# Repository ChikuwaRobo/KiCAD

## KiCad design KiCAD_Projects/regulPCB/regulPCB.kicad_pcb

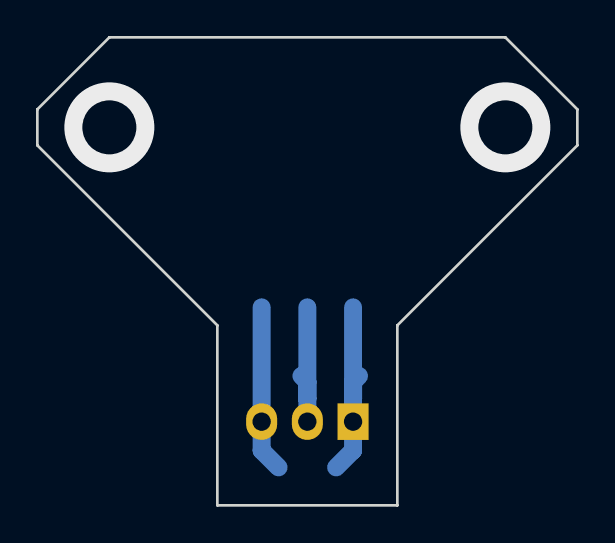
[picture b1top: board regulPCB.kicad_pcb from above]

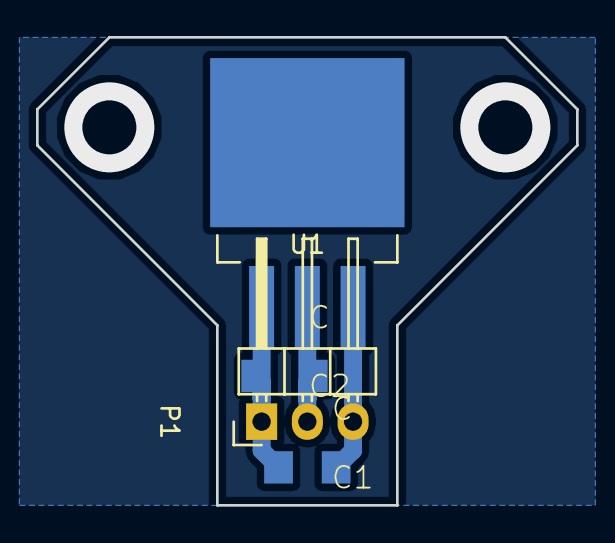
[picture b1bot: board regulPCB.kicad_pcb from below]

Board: 2 copper layers, 30.0 x 26.0 mm, 4 parts (4 on the bottom side), 3 nets.

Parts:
C1, C2: C; C3216
P1: CONN_01X03; Pin_Header_Angled_1x03
U1: LM1084IT-5.0/NOPB; TO-263-3Lead

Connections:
unnamed: C1.1, P1.3, U1.3
unnamed: C1.2, C2.2, P1.1, U1.1
unnamed: C2.1, P1.2, U1.2

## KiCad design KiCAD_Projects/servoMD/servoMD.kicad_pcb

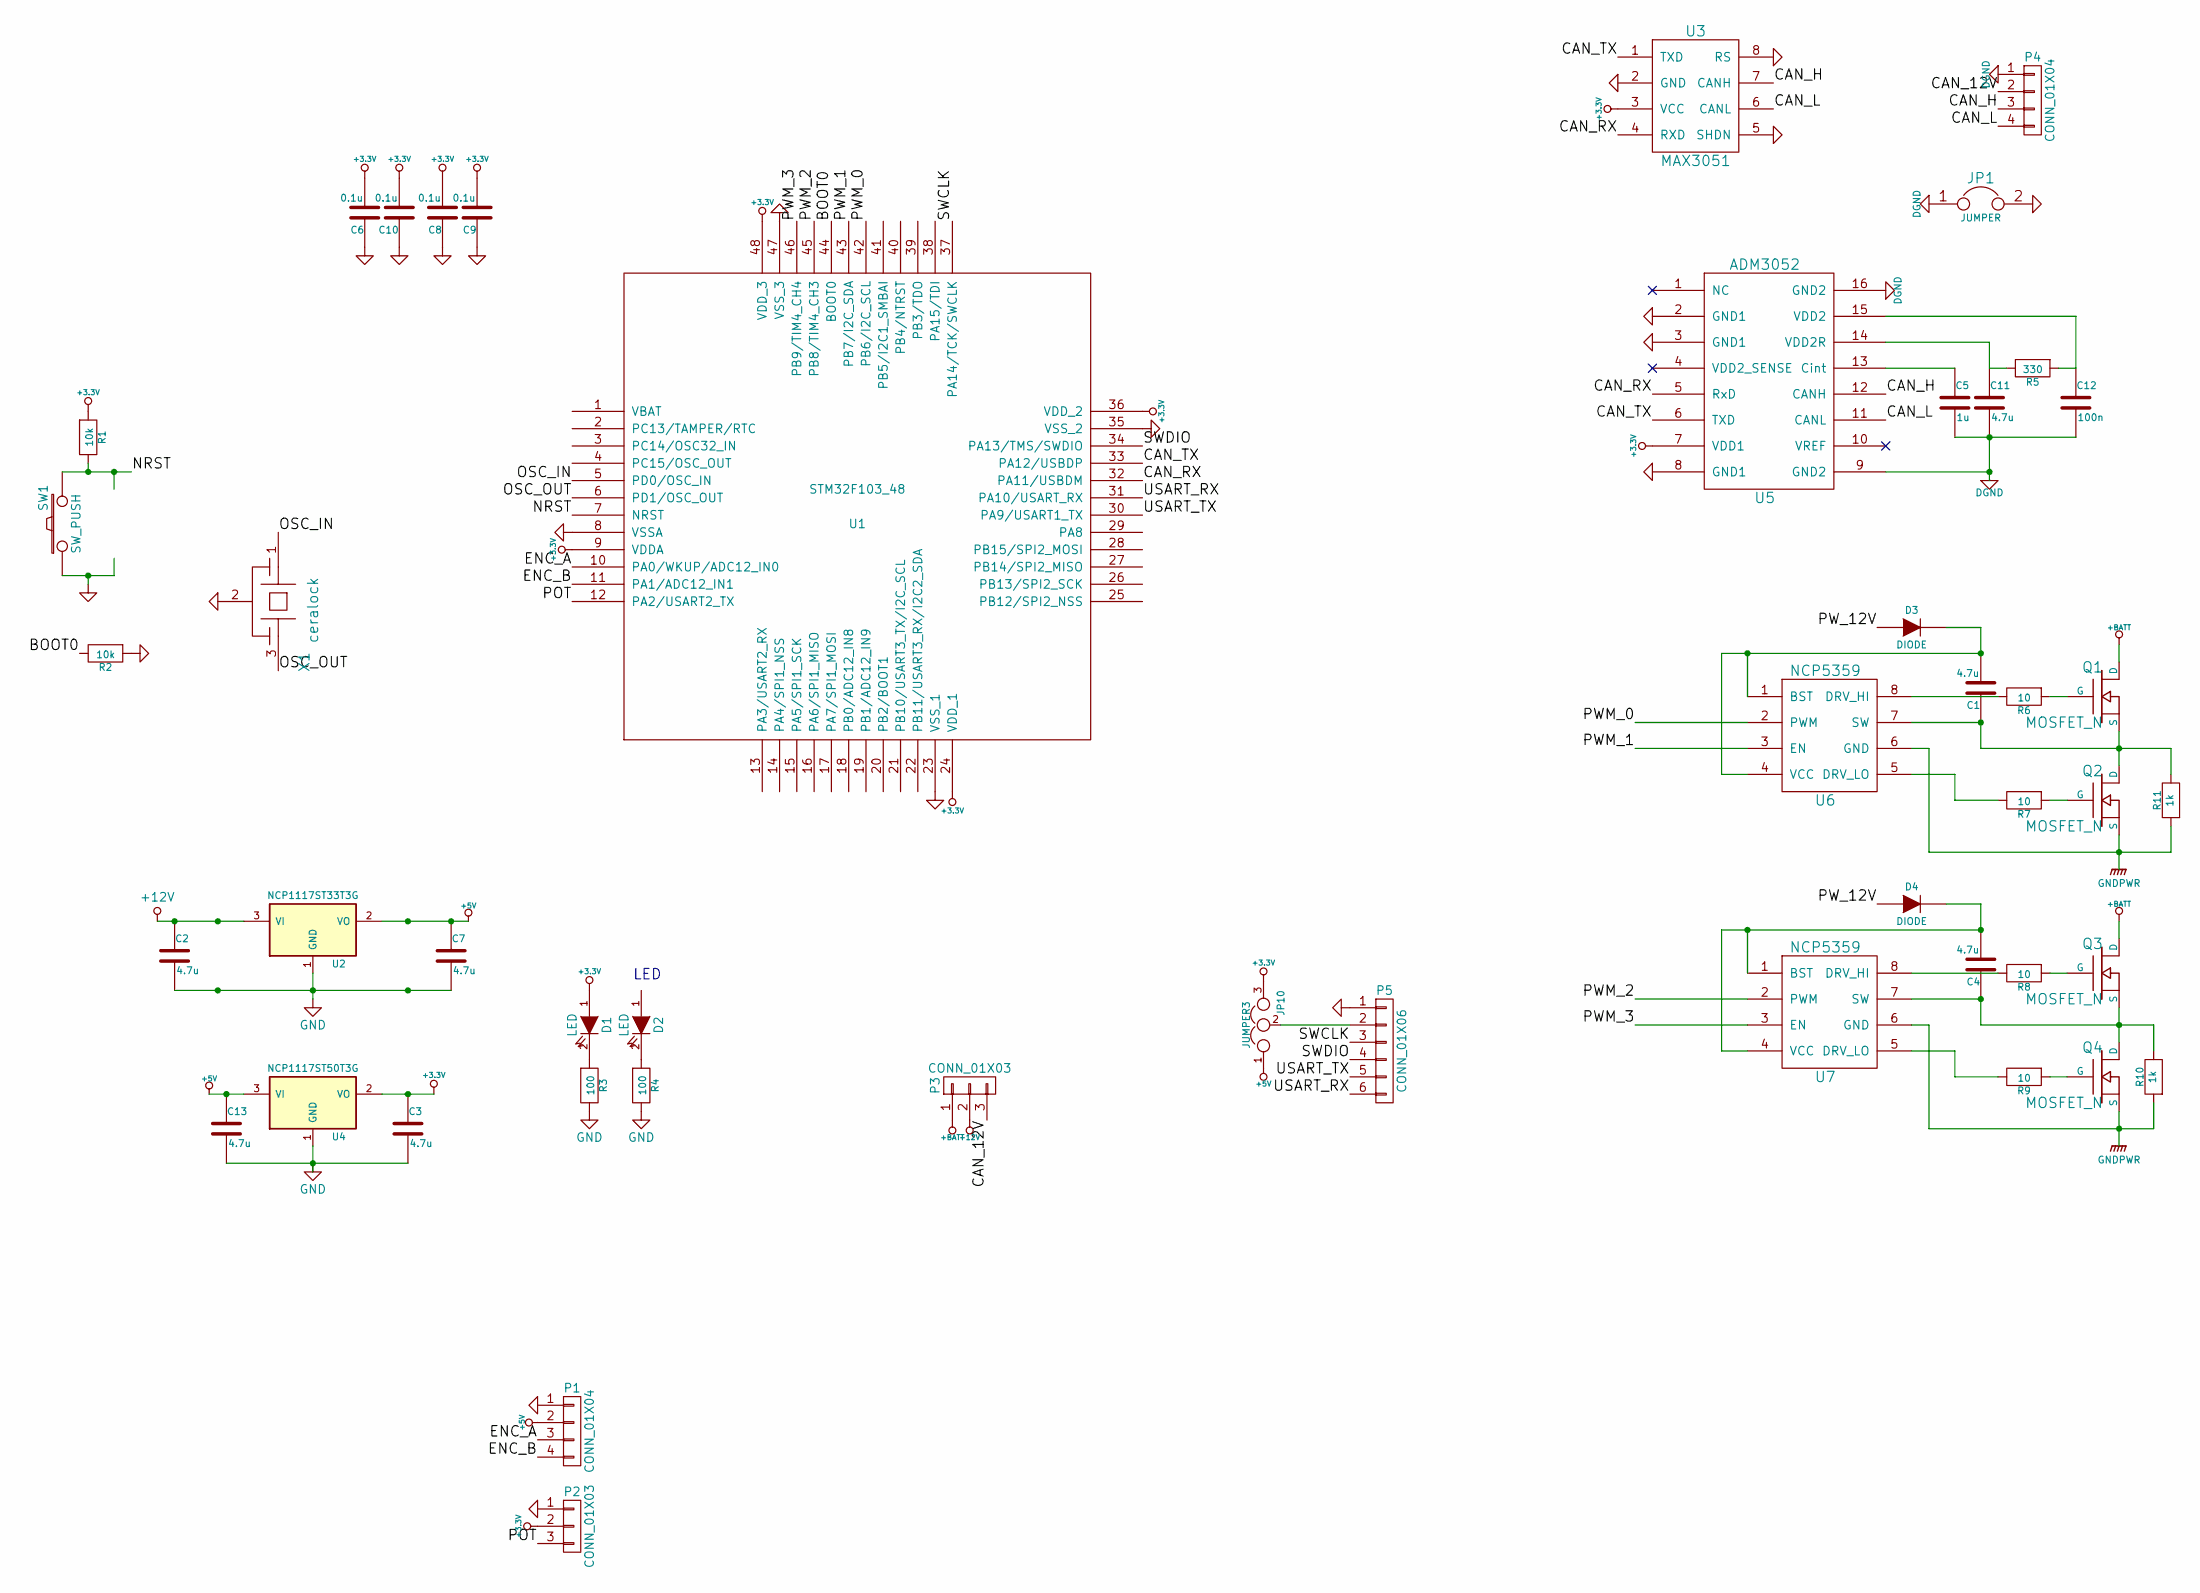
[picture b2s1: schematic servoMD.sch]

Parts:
C1, C2, C3, C4, C7, C11, C13: 4.7u; C3216_S
C5: 1u; C1608_WP_S
C6, C8, C9, C10: 0.1u; C1608_WP_S
C12: 100n; C1608_WP_S
D1, D2: LED; LED_0805
D3, D4: DIODE; C1608_WP_S
JP1: JUMPER; GS2
JP10: JUMPER3; GS3
P1, P4: CONN_01X04; XA_4T
P2: CONN_01X03; XA_3T
P3: CONN_01X03; Pin_Header_Straight_1x03
P5: CONN_01X06; ZH_6T
Q1, Q2, Q3, Q4: MOSFET_N; SOT-428_GDS
R1, R2: 10k; C1608_WP_S
R3, R4: 100; C1608_WP_S
R5: 330; C3225
R6, R7, R8, R9: 10; C1608_WP_S
R10, R11: 1k; C1608_WP_S
SW1: SW_PUSH; SW_SPST_EVQPE1
U1: STM32F103_48; LQFP-48_7x7mm_Pitch0.5mm
U2: NCP1117ST33T3G; SOT-223_reg
U3: MAX3051; SOIC-8_3.9x4.9mm_Pitch1.27mm_S
U4: NCP1117ST50T3G; SOT-223_reg
U5: ADM3052; SOIC-16_7.5x10.3mm_Pitch1.27mm
U6, U7: NCP5359; SOIC-8_3.9x4.9mm_Pitch1.27mm
X1: ceralock; Resonator_3×1.3mm

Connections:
+3.3V: C3.1, C6.2, C8.2, C9.2, C10.2, D1.1 (A), JP10.3, P2.2, R1.1, U1.9 (VDDA), U1.24 (VDD_1), U1.36 (VDD_2), U1.48 (VDD_3), U3.3 (VCC), U4.2 (VO), U5.7 (VDD1)
+5V: C7.1, C13.1, JP10.1, P1.2, U2.2 (VO), U4.3 (VI)
+12V: C2.1, P3.2, U2.3 (VI)
+BATT: P3.1, Q1.D, Q3.D
/BOOT0: R2.2, U1.44 (BOOT0)
/CAN_12V: P3.3, P4.2
/CAN_H: P4.3, U3.7 (CANH), U5.12 (CANH)
/CAN_L: P4.4, U3.6 (CANL), U5.11 (CANL)
/CAN_RX: U1.32 (PA11/USBDM), U3.4 (RXD), U5.5 (RxD)
/CAN_TX: U1.33 (PA12/USBDP), U3.1 (TXD), U5.6 (TXD)
/ENC_A: P1.3, U1.10 (PA0/WKUP/ADC12_IN0)
/ENC_B: P1.4, U1.11 (PA1/ADC12_IN1)
/NRST: R1.2, SW1.2, U1.7 (NRST)
/OSC_IN: U1.5 (PD0/OSC_IN), X1.1
/OSC_OUT: U1.6 (PD1/OSC_OUT), X1.3
/POT: P2.3, U1.12 (PA2/USART2_TX)
/PWM_0: U1.42 (PB6/I2C_SCL), U6.2 (PWM)
/PWM_1: U1.43 (PB7/I2C_SDA), U6.3 (EN)
/PWM_2: U1.45 (PB8/TIM4_CH3), U7.2 (PWM)
/PWM_3: U1.46 (PB9/TIM4_CH4), U7.3 (EN)
/PW_12V: D3.2 (A), D4.2 (A)
/SWCLK: P5.3, U1.37 (PA14/TCK/SWCLK)
/SWDIO: P5.4, U1.34 (PA13/TMS/SWDIO)
/USART_RX: P5.6, U1.31 (PA10/USART_RX)
/USART_TX: P5.5, U1.30 (PA9/USART1_TX)
DGND: C5.2, C11.2, C12.2, JP1.1, P4.1, U5.9 (GND2), U5.16 (GND2)
GND: C2.2, C3.2, C6.1, C7.2, C8.1, C9.1, C10.1, C13.2, JP1.2, P1.1, P2.1, P5.1, R2.1, R3.2, R4.2, SW1.1, U1.8 (VSSA), U1.23 (VSS_1), U1.35 (VSS_2), U1.47 (VSS_3), U2.1 (GND), U3.2 (GND), U3.5 (SHDN), U3.8 (RS), U4.1 (GND), U5.2 (GND1), U5.3 (GND1), U5.8 (GND1), X1.2
GNDPWR: Q2.S, Q4.S, R10.1, R11.1, U6.6 (GND), U7.6 (GND)
unnamed: C1.1, Q1.S, Q2.D, R11.2, U6.7 (SW)
unnamed: C1.2, D3.1 (K), U6.1 (BST), U6.4 (VCC)
unnamed: C4.1, Q3.S, Q4.D, R10.2, U7.7 (SW)
unnamed: C4.2, D4.1 (K), U7.1 (BST), U7.4 (VCC)
unnamed: C5.1, U5.13 (Cint)
unnamed: C11.1, R5.2, U5.14 (VDD2R)
unnamed: C12.1, R5.1, U5.15 (VDD2)
unnamed: D1.2 (K), R3.1
unnamed: D2.2 (K), R4.1
unnamed: JP10.2, P5.2
unnamed: Q1.G, R6.1
unnamed: Q2.G, R7.1
unnamed: Q3.G, R8.1
unnamed: Q4.G, R9.1
unnamed: R6.2, U6.8 (DRV_HI)
unnamed: R7.2, U6.5 (DRV_LO)
unnamed: R8.2, U7.8 (DRV_HI)
unnamed: R9.2, U7.5 (DRV_LO)

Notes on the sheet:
LED

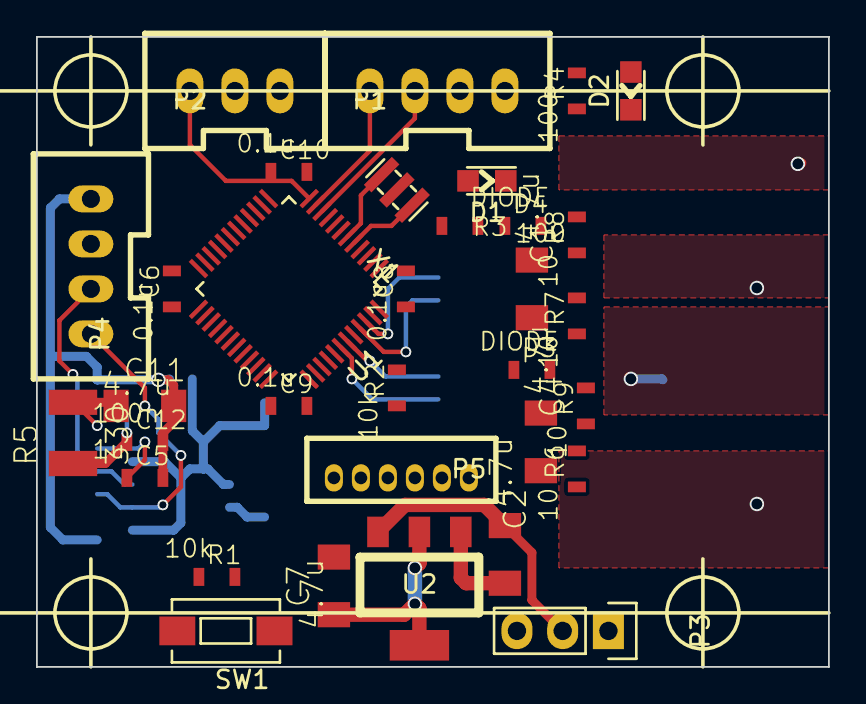
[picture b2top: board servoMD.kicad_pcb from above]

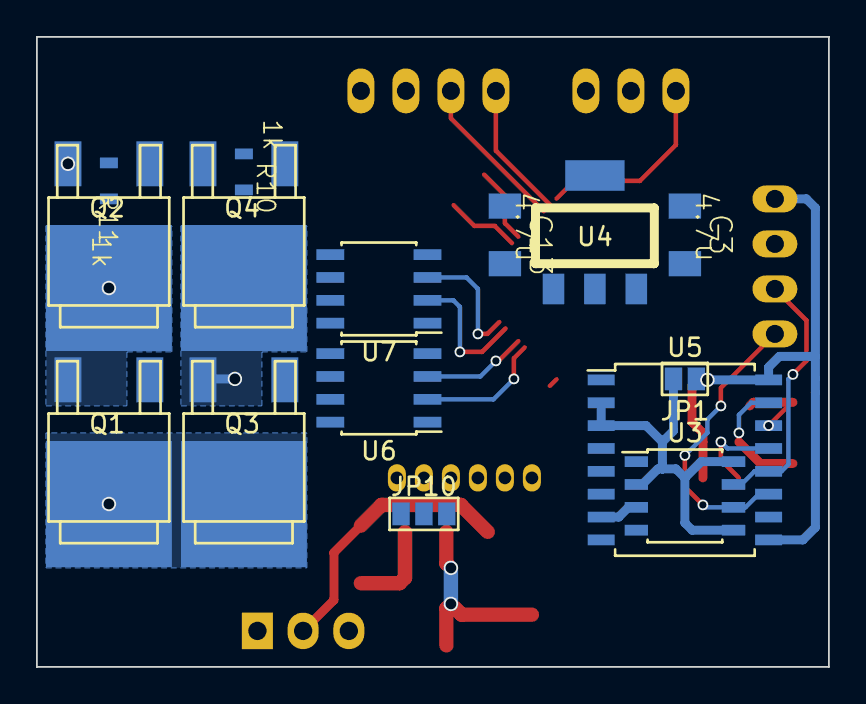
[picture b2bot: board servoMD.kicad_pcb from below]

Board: 2 copper layers, 44.0 x 35.0 mm, 48 parts (15 on the bottom side), 46 nets.

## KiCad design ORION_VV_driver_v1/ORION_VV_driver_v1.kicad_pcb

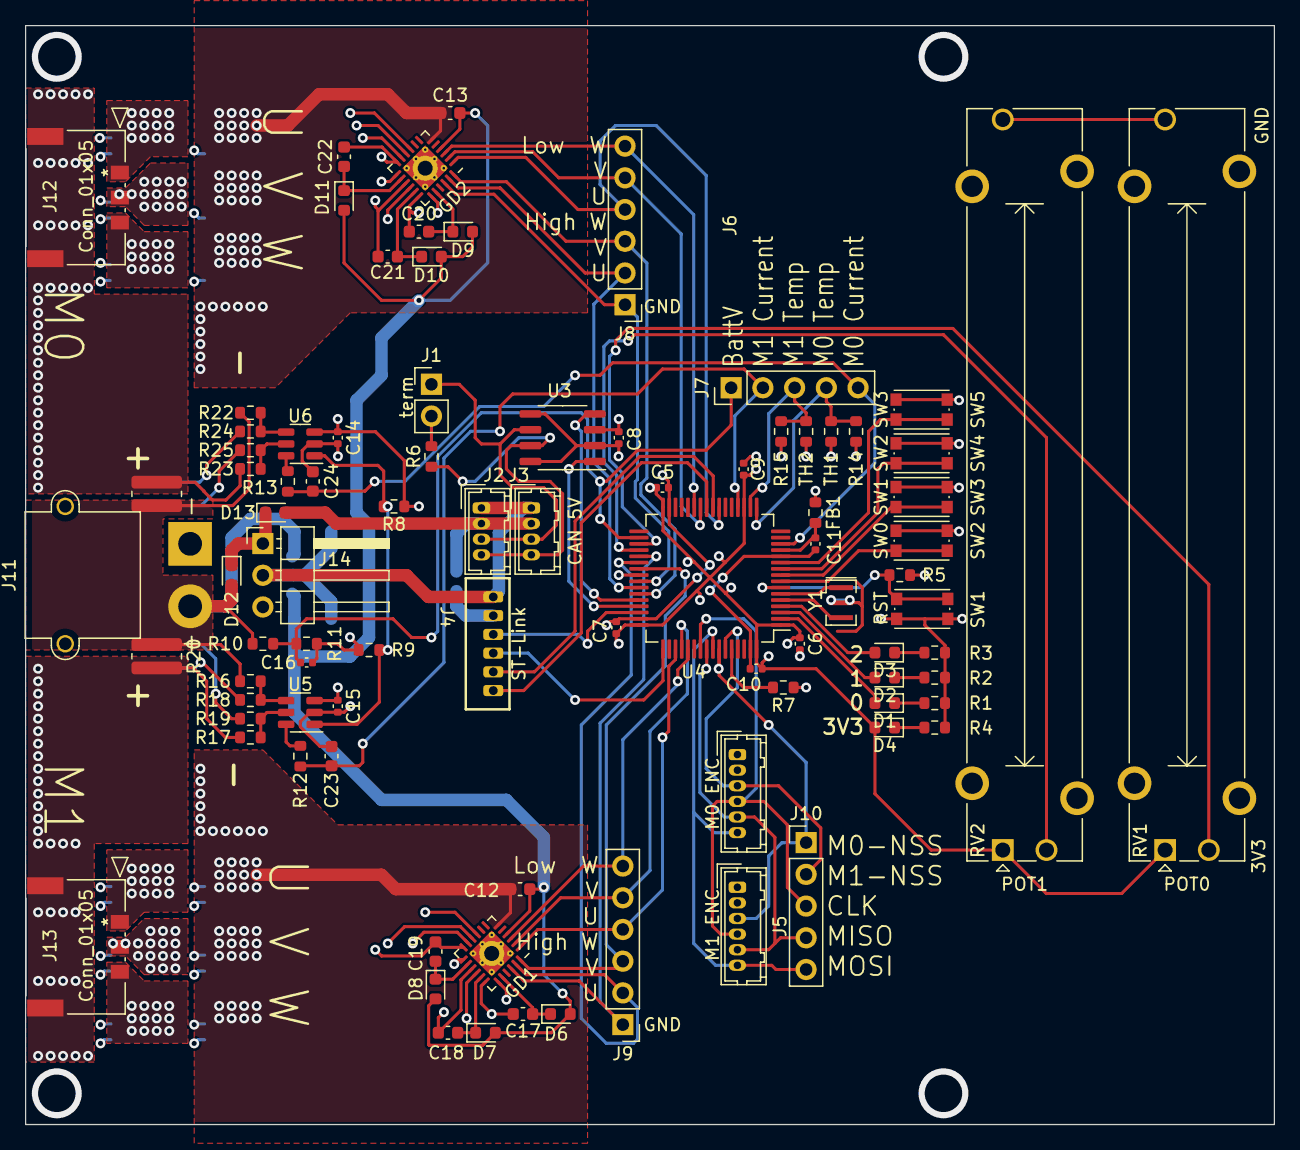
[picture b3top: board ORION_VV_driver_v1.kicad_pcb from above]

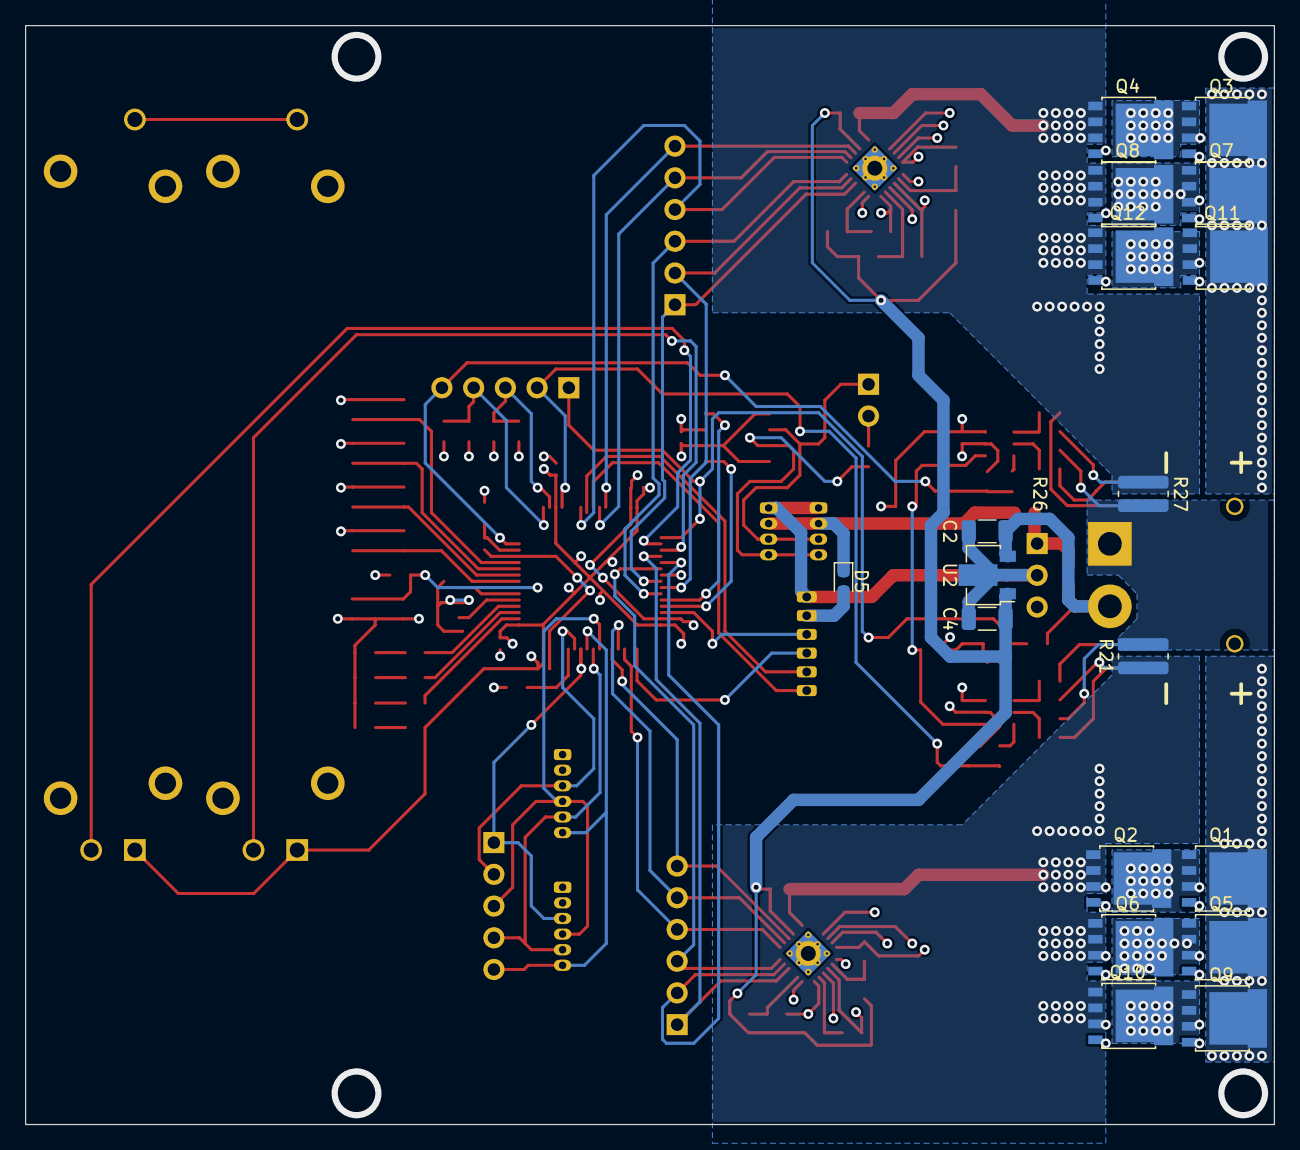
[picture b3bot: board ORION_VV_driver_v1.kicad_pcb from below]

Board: 4 copper layers, 100.0 x 88.0 mm, 106 parts (18 on the bottom side), 92 nets.

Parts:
C2, C4: 4.7u; C_1206_3216Metric
C5, C6, C7, C8, C9, C10, C11, C14, C15, C16: 0.1u; C_0402_1005Metric
C12, C13: 0.1u; C_0603_1608Metric
C17, C18, C19, C20, C21, C22, C23, C24: 1u; C_0603_1608Metric
D1, D2, D3, D4: LED; LED_0603_1608Metric
D5, D6, D7, D8, D9, D10, D11, D12, D13: D; D_0603_1608Metric
FB1: FB100; R_0603_1608Metric
GD1, GD2: FD6288Q; QFN-24-1EP_4x4mm_P0.5mm_EP2.6x2.6mm_ThermalVias
J1: Conn_01x02; PinHeader_1x02_P2.54mm_Vertical
J2, J3: Conn_01x04; Hirose_DF13-04P-1.25DSA_1x04_P1.25mm_Vertical
J4: Conn_01x06; ZH_B6B-ZR
J5, J6: Conn_01x06; Hirose_DF13-06P-1.25DSA_1x06_P1.25mm_Vertical
J7, J10: Conn_01x05; PinHeader_1x05_P2.54mm_Vertical
J8, J9: Conn_01x06; PinHeader_1x06_P2.54mm_Vertical
J11: Conn_01x02; AMASS_XT30PW-M_1x02_P2.50mm_Horizontal
J12, J13: Conn_01x05; 2053380003
J14: Conn_01x03; PinHeader_1x03_P2.54mm_Horizontal
Q1, Q2, Q3, Q4, Q5, Q6, Q7, Q8, Q9, Q10, Q11, Q12: IRF8721PBF-1; LFPAK56
R1, R2, R3, R4: 4.7k; R_0603_1608Metric
R5, R7, R11: 1k; R_0603_1608Metric
R6: 120; R_0603_1608Metric
R8, R9, R12, R13, R16, R17, R18, R19, R22, R23, R24, R25: 100; R_0603_1608Metric
R10, R14, R15: 10k; R_0603_1608Metric
R20, R21, R26, R27: 10m; R_0815_2038Metric
RV1, RV2: R_Potentiometer; Potentiometer_Bourns_PTA4543_Single_Slide
SW1, SW2, SW3, SW4, SW5: SW_Push; SW_Push_1P1T_NO_CK_KMR2
TH1, TH2: Thermistor; R_0603_1608Metric
U2: L78L15_SOT89; SOT-89-3
U3: MAX3051; SO-8_3.9x4.9mm_P1.27mm
U4: LQFP-64_10x10mm_P0.5mm
U5, U6: INA199; TSOT-23-6
Y1: Resonator; Resonator_SMD_Murata_CSTxExxV-3Pin_3.0x1.1mm

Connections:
+3V3: C5.2, C6.2, C7.2, C8.2, C9.2, C10.2, C14.2, C15.2, D4.2 (A), FB1.1, J5.2, J6.2, J14.3, R5.2, R8.1, RV1.1, RV2.1, TH1.1, TH2.1, U3.3 (VDD), U4.1 (VBAT), U4.19 (VDD), U4.32 (VDD), U4.48 (VDD), U4.64 (VDD), U5.3 (VDD), U6.3 (VDD)
+5V: D5.1 (K), D13.2 (A), J2.2, J3.2
+15V: C4.2, C12.2, C13.2, D6.2 (A), D7.2 (A), D8.2 (A), D9.2 (A), D10.2 (A), D11.2 (A), GD1.4 (VCC), GD2.4 (VCC), U2.1 (OUT)
+BATT: C2.2, D12.2 (A), J11.2, R10.1, R16.1, R20.1, R22.1, R26.1, U2.3 (IN)
/3V3_HARF_REF: R8.2, R9.1, U5.1 (REF), U6.1 (REF)
/BATT_V_SENS: C16.2, J7.1, R10.2, R11.1, U4.34 (PB13)
/CAN_H: J2.4, J3.4, R6.1, U3.7 (CANH)
/CAN_L: J1.1, J2.3, J3.3, U3.6 (CANL)
/CAN_RX: U3.4 (RXD), U4.44 (PA11)
/CAN_TX: U3.1 (TXD), U4.45 (PA12)
/LED_0: D1.2 (A), U4.2 (PC13)
/LED_1: D2.2 (A), U4.3 (PC14)
/LED_2: D3.2 (A), U4.4 (PC15)
/M0_CS: C24.2, J7.5, R13.1, U4.14 (PA0)
/M0_CSH: R22.2, R24.2, U6.4 (IN+)
/M0_CSL: R23.2, R25.2, U6.5 (IN-)
/M0_U: C22.1, GD2.12 (VS3), J12.1, Q3.1 (S), Q3.2 (S), Q3.3 (S), Q4.5 (D)
/M0_UH: GD2.22 (HIN1), J8.1, U4.41 (PA8)
/M0_UL: GD2.1 (LIN1), J8.4, U4.23 (PA7)
/M0_V: C21.1, GD2.15 (VS2), J12.2, Q7.1 (S), Q7.2 (S), Q7.3 (S), Q8.5 (D)
/M0_VH: GD2.23 (HIN2), J8.2, U4.42 (PA9)
/M0_VL: GD2.2 (LIN2), J8.5, U4.26 (PB0)
/M0_W: C20.1, GD2.18 (VS1), J12.3, Q11.1 (S), Q11.2 (S), Q11.3 (S), Q12.5 (D)
/M0_WH: GD2.24 (HIN3), J8.3, U4.43 (PA10)
/M0_WL: GD2.3 (LIN3), J8.6, U4.27 (PB1)
/M1_CS: C23.2, J7.2, R12.1, U4.20 (PA4)
/M1_CSH: R16.2, R18.2, U5.4 (IN+)
/M1_CSL: R17.2, R19.2, U5.5 (IN-)
/M1_U: C19.1, GD1.12 (VS3), J13.1, Q1.1 (S), Q1.2 (S), Q1.3 (S), Q2.5 (D)
/M1_UH: GD1.22 (HIN1), J9.1, U4.37 (PC6)
/M1_UL: GD1.1 (LIN1), J9.4, U4.51 (PC10)
/M1_V: C18.1, GD1.15 (VS2), J13.2, Q5.1 (S), Q5.2 (S), Q5.3 (S), Q6.5 (D)
/M1_VH: GD1.23 (HIN2), J9.2, U4.38 (PC7)
/M1_VL: GD1.2 (LIN2), J9.5, U4.52 (PC11)
/M1_W: C17.1, GD1.18 (VS1), J13.3, Q9.1 (S), Q9.2 (S), Q9.3 (S), Q10.5 (D)
/M1_WH: GD1.24 (HIN3), J9.3, U4.39 (PC8)
/M1_WL: GD1.3 (LIN3), J9.6, U4.53 (PC12)
/NRST: R5.1, SW1.2, U4.7 (NRST)
/NSS_ENC0: J5.3, J10.1, U4.58 (PB6)
/NSS_ENC1: J6.3, J10.2, U4.59 (PB7)
/OSC_IN: U4.5 (PF0), Y1.3
/OSC_OUT: U4.6 (PF1), Y1.1
/POT_0: RV1.2, U4.35 (PB14)
/POT_1: RV2.2, U4.36 (PB15)
/SPI_CLK: J5.4, J6.4, J10.3, U4.55 (PB3)
/SPI_MISO: J5.5, J6.5, J10.4, U4.56 (PB4)
/SPI_MOSI: J5.6, J6.6, J10.5, U4.57 (PB5)
/SW0: SW2.2, U4.8 (PC0)
/SW1: SW3.2, U4.9 (PC1)
/SW2: SW4.2, U4.10 (PC2)
/SW3: SW5.2, U4.11 (PC3)
/SWCLK: J4.4, U4.49 (PA14)
/SWDIO: J4.3, U4.46 (PA13)
/TEMP_0: J7.4, R14.1, TH1.2, U4.17 (PA3)
/TEMP_1: J7.3, R15.1, TH2.2, U4.18 (PF4)
/UART1_RX: J4.6, U4.25 (PC5)
/UART1_TX: J4.5, U4.24 (PC4)
GND: C2.1, C4.1, C5.1, C6.1, C7.1, C8.1, C9.1, C10.1, C11.1, C14.1, C15.1, C16.1, C23.1, C24.1, J2.1, J3.1, J4.1, J5.1, J6.1, J14.2, R1.1, R2.1, R3.1, R4.1, R7.1, R9.2, R11.2, R14.2, R15.2, RV1.3, RV2.3, SW1.1, SW2.1, SW3.1, SW4.1, SW5.1, U2.2 (GND), U3.2 (GND), U3.5 (SHDN), U3.8 (RS), U4.12 (VSSA), U4.31 (VSS), U4.47 (VSS), U4.63 (VSS), U5.2 (GND), U6.2 (GND), Y1.2
GNDPWR: J11.1, R19.1, R21.2, R25.1, R27.2
unnamed: C11.2, FB1.2, U4.13 (VDDA)
unnamed: C12.1, GD1.6 (COM), Q2.1 (S), Q2.2 (S), Q2.3 (S), Q6.1 (S), Q6.2 (S), Q6.3 (S), Q10.1 (S), Q10.2 (S), Q10.3 (S), R18.1, R21.1
unnamed: C13.1, GD2.6 (COM), Q4.1 (S), Q4.2 (S), Q4.3 (S), Q8.1 (S), Q8.2 (S), Q8.3 (S), Q12.1 (S), Q12.2 (S), Q12.3 (S), R24.1, R27.1
unnamed: C17.2, D6.1 (K), GD1.20 (VB1)
unnamed: C18.2, D7.1 (K), GD1.17 (VB2)
unnamed: C19.2, D8.1 (K), GD1.14 (VB3)
unnamed: C20.2, D9.1 (K), GD2.20 (VB1)
unnamed: C21.2, D10.1 (K), GD2.17 (VB2)
unnamed: C22.2, D11.1 (K), GD2.14 (VB3)
unnamed: D1.1 (K), R1.2
unnamed: D2.1 (K), R2.2
unnamed: D3.1 (K), R3.2
unnamed: D4.1 (K), R4.2
unnamed: D5.2 (A), J4.2
unnamed: D12.1 (K), D13.1 (K), J14.1
unnamed: GD1.9 (LO3), Q2.4 (G)
unnamed: GD1.10 (LO2), Q6.4 (G)
unnamed: GD1.11 (LO1), Q10.4 (G)
unnamed: GD1.13 (HO3), Q1.4 (G)
unnamed: GD1.16 (HO2), Q5.4 (G)
unnamed: GD1.19 (HO1), Q9.4 (G)
unnamed: GD2.9 (LO3), Q4.4 (G)
unnamed: GD2.10 (LO2), Q8.4 (G)
unnamed: GD2.11 (LO1), Q12.4 (G)
unnamed: GD2.13 (HO3), Q3.4 (G)
unnamed: GD2.16 (HO2), Q7.4 (G)
unnamed: GD2.19 (HO1), Q11.4 (G)
unnamed: J1.2, R6.2
unnamed: J12.4, J12.5, Q3.5 (D), Q7.5 (D), Q11.5 (D), R23.1, R26.2
unnamed: J13.4, J13.5, Q1.5 (D), Q5.5 (D), Q9.5 (D), R17.1, R20.2
unnamed: R7.2, U4.60 (BOOT0)
unnamed: R12.2, U5.6 (OUT)
unnamed: R13.2, U6.6 (OUT)

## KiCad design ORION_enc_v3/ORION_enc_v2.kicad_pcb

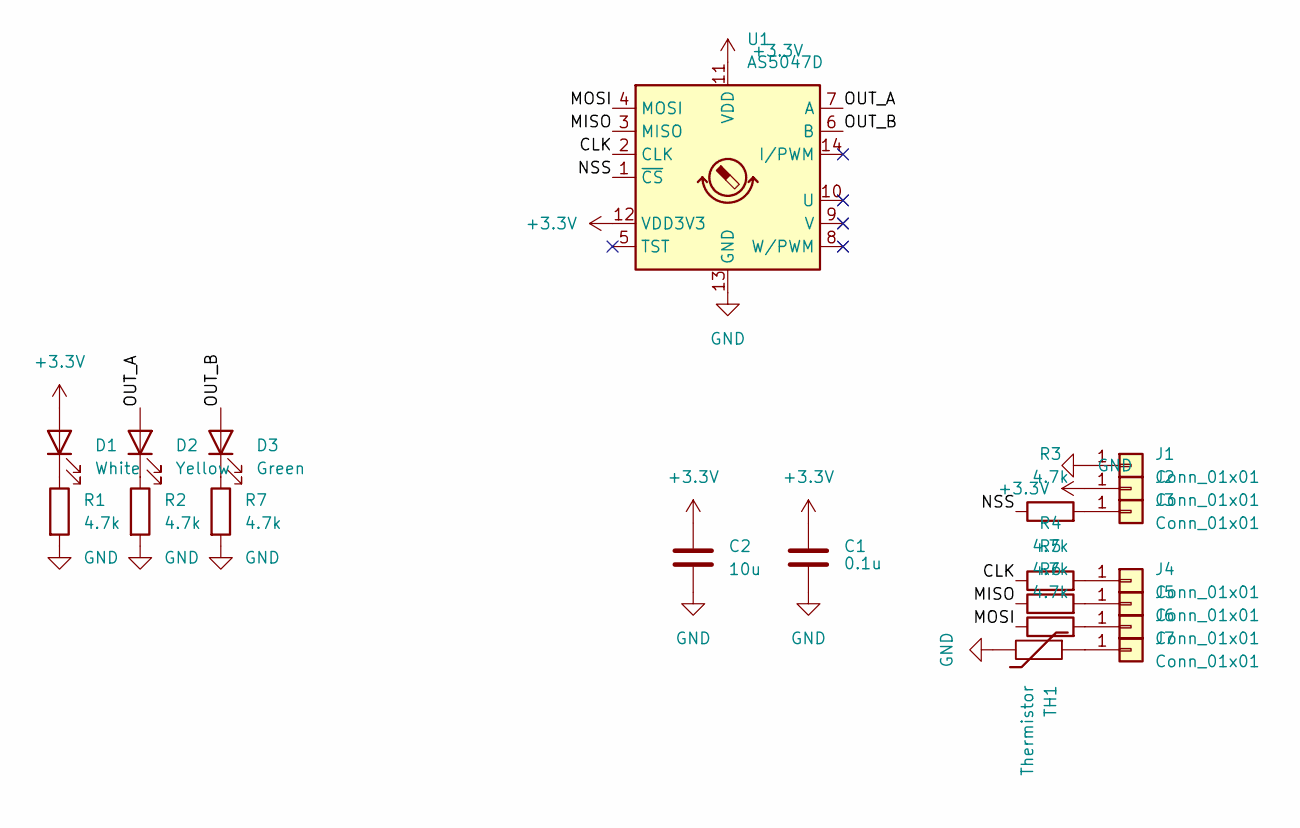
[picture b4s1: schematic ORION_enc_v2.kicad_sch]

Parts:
C1: 0.1u; C_0603_1608Metric
C2: 10u; C_0603_1608Metric
D1: White; LED_0603_1608Metric
D2: Yellow; LED_0603_1608Metric
D3: Green; LED_0603_1608Metric
J1, J2, J3, J4, J5, J6, J7: Conn_01x01; WireSoldingPad
R1, R2, R3, R4, R5, R6, R7: 4.7k; R_0603_1608Metric
TH1: Thermistor; R_0603_1608Metric
U1: AS5047D; TSSOP-14_4.4x5mm_P0.65mm

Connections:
+3V3: C1.1, C2.1, D1.2 (A), J2.1, U1.11 (VDD), U1.12 (VDD3V3)
/CLK: R4.1, U1.2 (CLK)
/MISO: R5.1, U1.3 (MISO)
/MOSI: R6.1, U1.4 (MOSI)
/NSS: R3.1, U1.1 (~CS)
/OUT_A: D2.2 (A), U1.7 (A)
/OUT_B: D3.2 (A), U1.6 (B)
GND: C1.2, C2.2, J1.1, R1.2, R2.2, R7.2, TH1.2, U1.5 (TST), U1.13 (GND)
unnamed: D1.1 (K), R1.1
unnamed: D2.1 (K), R2.1
unnamed: D3.1 (K), R7.1
unnamed: J3.1, R3.2
unnamed: J4.1, R4.2
unnamed: J5.1, R5.2
unnamed: J6.1, R6.2
unnamed: J7.1, TH1.1

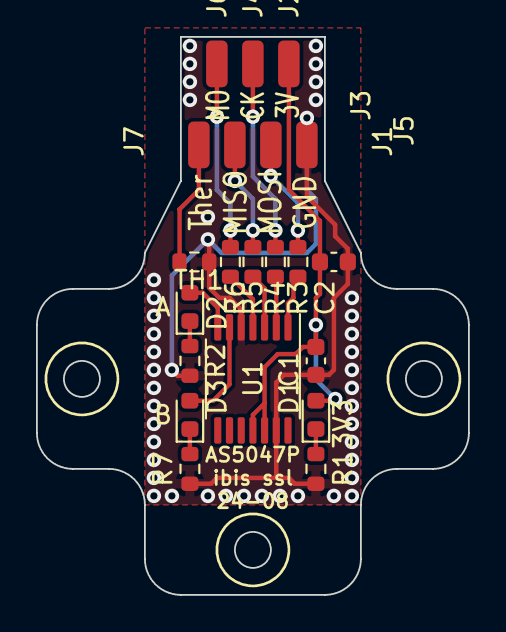
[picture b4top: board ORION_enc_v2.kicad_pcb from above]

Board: 2 copper layers, 24.0 x 31.0 mm, 21 parts (0 on the bottom side), 16 nets.

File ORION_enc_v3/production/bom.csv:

Designator,Footprint,Quantity,Value,LCSC Part #
C1,C_0603_1608Metric,1,0.1u,
C2,C_0603_1608Metric,1,10u,
D1,LED_0603_1608Metric,1,White,
D2,LED_0603_1608Metric,1,Yellow,
D3,LED_0603_1608Metric,1,Green,
"J1, J2, J3, J4, J5, J6, J7",WireSoldingPad,7,Conn_01x01,
"R1, R2, R3, R4, R5, R6, R7",R_0603_1608Metric,7,4.7k,
TH1,R_0603_1608Metric,1,Thermistor,
U1,TSSOP-14_4.4x5mm_P0.65mm,1,AS5047D,

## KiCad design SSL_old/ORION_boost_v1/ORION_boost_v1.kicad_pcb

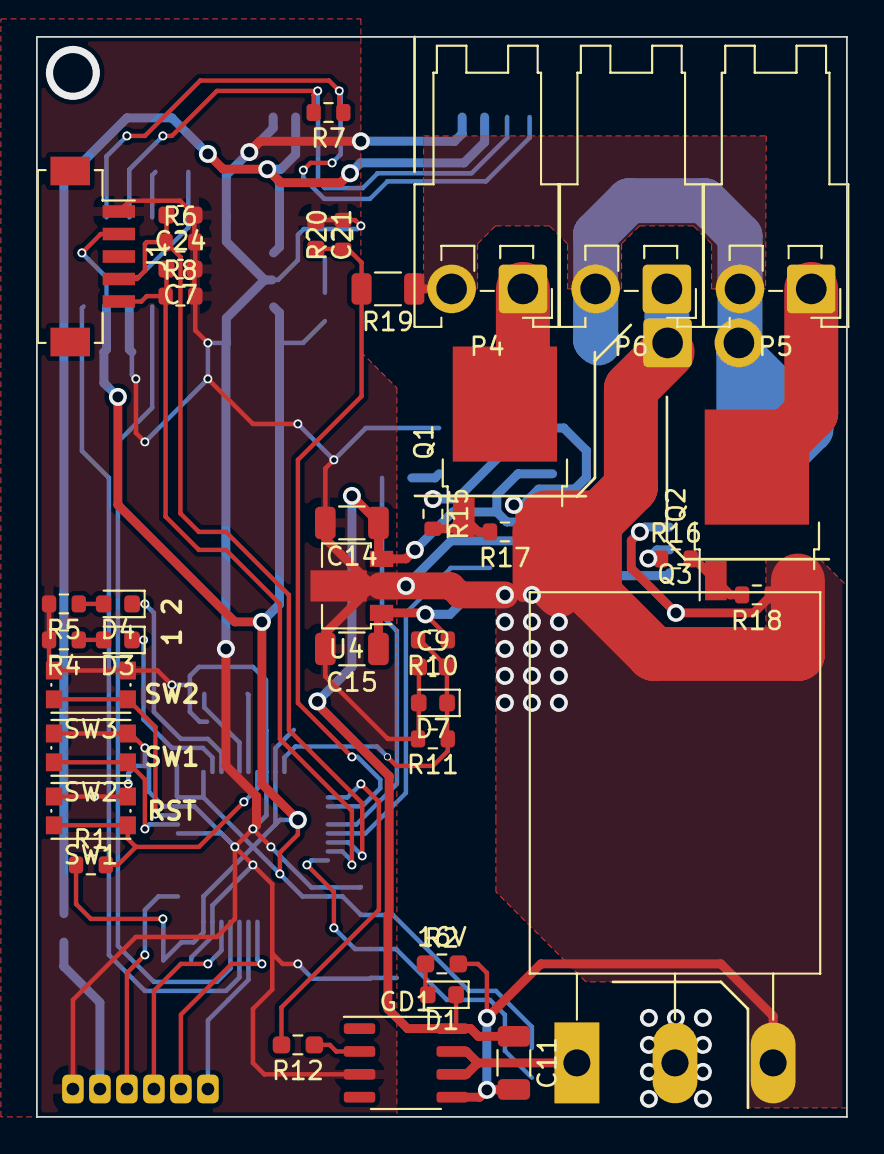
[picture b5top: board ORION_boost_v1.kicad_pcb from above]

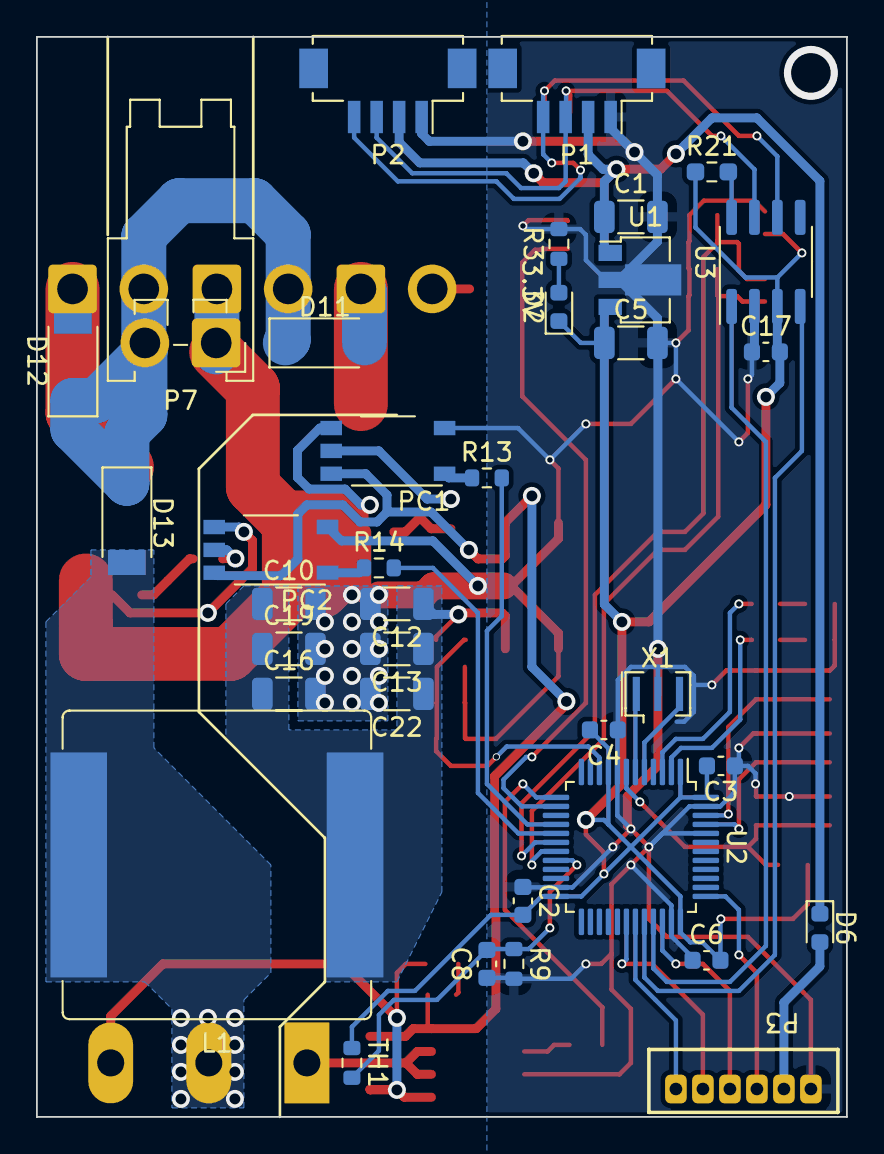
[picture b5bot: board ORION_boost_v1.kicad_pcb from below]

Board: 2 copper layers, 45.0 x 60.0 mm, 75 parts (36 on the bottom side), 46 nets.

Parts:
C1, C5, C10, C11, C12, C13, C14, C15, C16, C19, C22: 4.7u; C_1206_3216Metric
C2, C3, C4, C6, C7, C8, C9, C17, C21, C24: 0.1u; C_0603_1608Metric
D1, D2, D3, D4: LED; LED_0603_1608Metric
D6: D; D_0603_1608Metric
D7: D_Zener_3.3V; D_0603_1608Metric
D11, D12, D13: D; D_SOD-128
GD1: Si8261; SO-8_3.9x4.9mm_P1.27mm
J1: Conn_01x05; Hirose_DF13C_CL535-0405-0-51_1x05-1MP_P1.25mm_Vertical
L1: 10uH; L_Bourns_SRP1770TA_16.9x16.9mm
P1, P2: CONN_01X04; Hirose_DF13C_CL535-0404-8-51_1x04-1MP_P1.25mm_Vertical
P3: CONN_01X06; ZH_B6B-ZR
P4, P5, P6, P7: CONN_01X02; JST_VH_S2P-VH_1x02_P3.96mm_Horizontal
PC1, PC2: TLP117; MFSOP6-5_4.4x3.6mm_P1.27mm
Q1, Q2: Q_NMOS_GDS; TO-252-2
Q3: Q_NMOS_GDS; TO-247-3_Horizontal_TabDown
R1, R6, R8, R9, R10: 10k; R_0603_1608Metric
R2, R21: 1k; R_0603_1608Metric_Pad0.98x0.95mm_HandSolder
R3, R4, R5, R11, R17, R18: 1k; R_0603_1608Metric
R7: 120; R_0603_1608Metric
R12: 100; R_0603_1608Metric_Pad0.98x0.95mm_HandSolder
R13, R14: 100; R_0603_1608Metric
R15, R16: 10; R_0603_1608Metric
R19: 1M; R_1206_3216Metric
R20: 4.7k; R_0603_1608Metric
SW1, SW2, SW3: SW_Push; SW_Push_1P1T_NO_CK_KMR2
TH1: Thermistor; R_0603_1608Metric
U1, U4: LM7805CT; SOT-89-3
U2: STM32F103_48; LQFP-48_7x7mm_P0.5mm
U3: LTC2875-S8; SOIC-8_3.9x4.9mm_P1.27mm
X1: ceralock; Resonator_SMD_Murata_CSTxExxV-3Pin_3.0x1.1mm

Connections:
+3.3V: C2.2, C3.2, C4.2, C5.1, C6.2, C17.2, D2.1 (K), J1.2, R1.1, R21.1, TH1.1, U1.3 (OUT), U2.1 (VBAT), U2.9 (VDDA), U2.24 (VDD_1), U2.36 (VDD_2), U2.48 (VDD_3), U3.3 (VCC)
+5V: C1.1, D6.1 (K), P1.2, P2.2, U1.1 (IN)
+BATT: C10.1, C12.1, C13.1, C15.1, C16.1, C19.1, C22.1, L1.1, R10.1, U4.1 (IN)
/16V: C11.1, C14.1, D1.1 (K), GD1.8 (VDD), PC1.6 (VCC), PC2.6 (VCC), U4.3 (OUT)
/BOOST_PWM: R12.2, U2.13 (PA3/USART2_RX)
/BattVsense: C9.2, D7.1 (K), R10.2, R11.1, U2.10 (PA0/WKUP/ADC12_IN0)
/BoostVsense: C21.2, R19.2, R20.1, U2.14 (PA4/SPI1_NSS)
/CAN_H: P1.3, P2.3, R7.2, U3.7 (CANH)
/CAN_L: P1.4, P2.4, R7.1, U3.6 (CANL)
/CAN_RX: U2.32 (PA11/CAN_RX/USBDM), U3.4 (RXD)
/CAN_TX: U2.33 (PA12/CAN_TX/USBDP), U3.1 (TXD)
/CAP_450V: D11.1 (K), D12.1 (K), D13.1 (K), P4.2, P5.2, P6.2, P7.2, R19.1
/Kick1: R13.2, U2.16 (PA6/SPI1_MISO)
/Kick2: R14.2, U2.17 (PA7/SPI1_MOSI)
/LED_1: D3.1 (K), U2.2 (PC13/TAMPER/RTC)
/LED_2: D4.1 (K), U2.3 (PC14/OSC32_IN)
/NRST: R1.2, SW1.1, U2.7 (NRST)
/OSC_IN: U2.5 (PD0/OSC_IN), X1.3
/OSC_OUT: U2.6 (PD1/OSC_OUT), X1.1
/SW1: SW2.1, U2.45 (PB8/TIM4_CH3)
/SW2: SW3.1, U2.46 (PB9/TIM4_CH4)
/SWCLK: P3.3, U2.37 (PA14/TCK/SWCLK)
/SWDIO: P3.4, U2.34 (PA13/TMS/SWDIO)
/TEMP_0: C24.2, J1.4, R6.1, U2.18 (PB0/ADC12_IN8)
/TEMP_1: C7.2, J1.5, R8.1, U2.19 (PB1/ADC12_IN9)
/TEMP_2: C8.2, R9.1, TH1.2, U2.20 (PB2/BOOT1)
/USART_RX: P3.6, U2.31 (PA10/USART_RX)
/USART_TX: P3.5, U2.30 (PA9/USART1_TX)
GND: C1.2, C2.1, C3.1, C4.1, C5.2, C6.1, C7.1, C8.1, C9.1, C10.2, C11.2, C12.2, C13.2, C14.2, C15.2, C16.2, C17.1, C19.2, C21.1, C22.2, C24.1, D7.2 (A), GD1.3 (K), GD1.5 (GND), J1.1, P1.1, P2.1, P3.1, P6.1, P7.1, PC1.3 (K), PC1.4 (GND), PC2.3 (K), PC2.4 (GND), Q1.3 (S), Q2.3 (S), Q3.3 (S), R2.2, R3.2, R4.2, R5.2, R6.2, R8.2, R9.2, R11.2, R17.1, R18.1, R20.2, SW1.2, SW2.2, SW3.2, U1.2 (GND), U2.8 (VSSA), U2.23 (VSS_1), U2.35 (VSS_2), U2.44 (BOOT0), U2.47 (VSS_3), U3.2 (GND), U4.2 (GND), X1.2
unnamed: D1.2 (A), R2.1
unnamed: D2.2 (A), R3.1
unnamed: D3.2 (A), R4.1
unnamed: D4.2 (A), R5.1
unnamed: D6.2 (A), P3.2
unnamed: D11.2 (A), P4.1, Q1.2 (D)
unnamed: D12.2 (A), P5.1, Q2.2 (D)
unnamed: D13.2 (A), L1.2, Q3.2 (D)
unnamed: GD1.2 (A), R12.1
unnamed: GD1.6 (VO), GD1.7 (VO), Q3.1 (G)
unnamed: PC1.1 (A), R13.1
unnamed: PC1.5 (VO), R15.1
unnamed: PC2.1 (A), R14.1
unnamed: PC2.5 (VO), R16.1
unnamed: Q1.1 (G), R15.2, R17.2
unnamed: Q2.1 (G), R16.2, R18.2
unnamed: R21.2, U3.8 (RS)

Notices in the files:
parts and their libraries:
Copyright 2021 Accelerated Designs. All rights reserved.
